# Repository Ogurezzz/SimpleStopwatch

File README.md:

# SimpleStopwatch

This is very simple stopwatch. I needed something that will count time when switch is On and reset when switch is off.
I found several solutions, but most of them are hardware worktime/switchOn counter. And you need to do some workaround to reset counter.

This SimpleStopwatch will solve my problem. It can count up to 99 hours. Uses up to 6 7-segment digits.

ToDo: 
1) (DONE) Make PCB with Atmega328, quartz, ULN2003 and indicators. With remote button/switch connection.
2) (DONE)Make 3D printed and CNC milled case for this Stopwatch. It should give me option for mounting to the panel of any device.

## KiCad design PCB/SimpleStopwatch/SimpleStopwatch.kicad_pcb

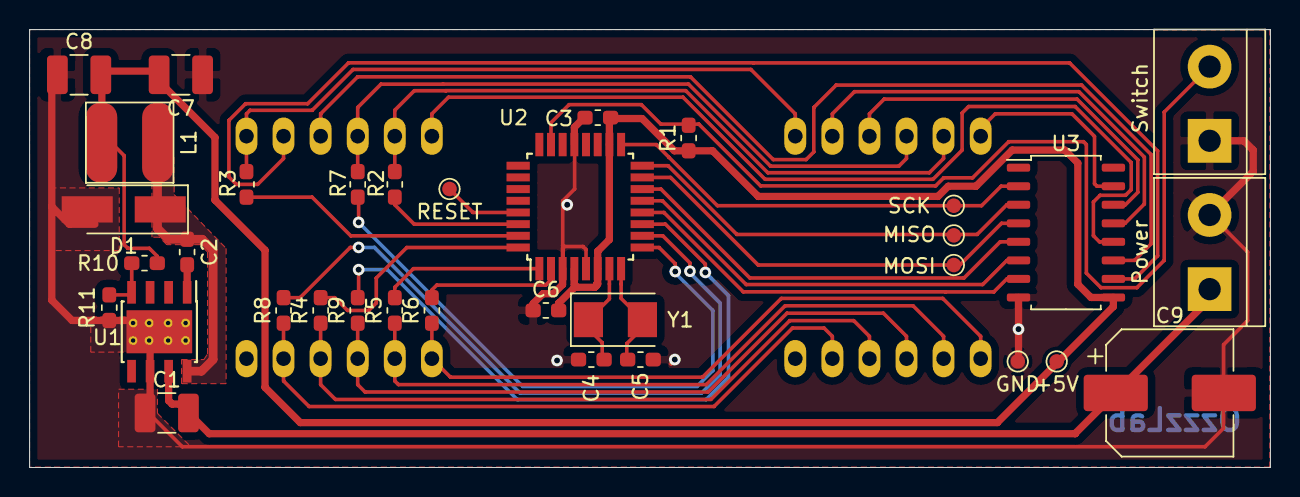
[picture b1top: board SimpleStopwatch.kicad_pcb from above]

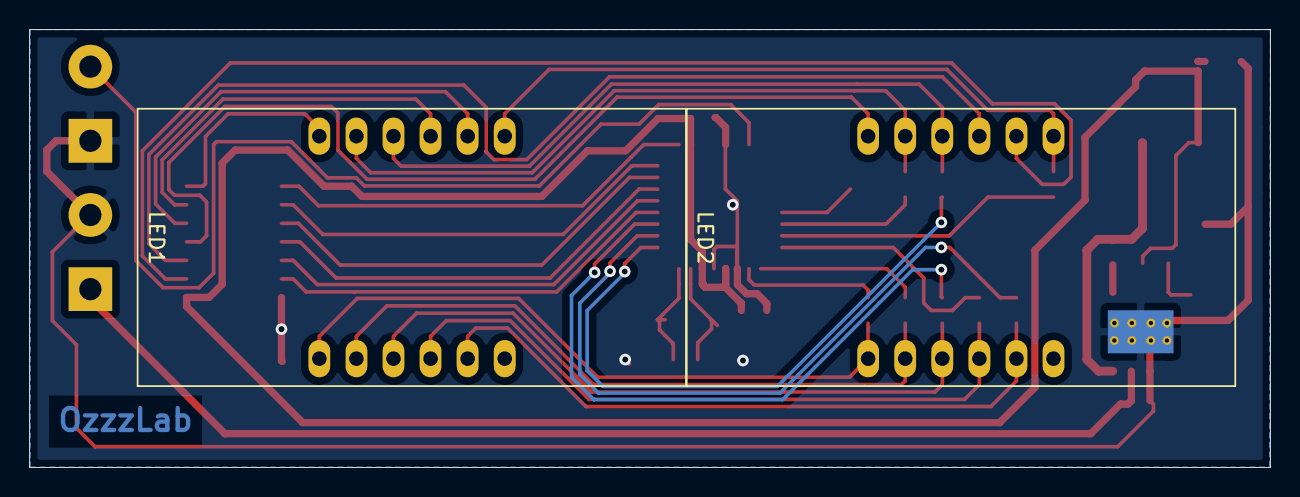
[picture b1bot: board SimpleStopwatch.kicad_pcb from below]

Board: 2 copper layers, 85.0 x 30.0 mm, 36 parts (2 on the bottom side), 38 nets.

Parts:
C1, C7, C8: 22u; C_1210_3225Metric_Pad1.42x2.65mm_HandSolder
C2, C3, C6: 0.1u; C_0603_1608Metric_Pad1.05x0.95mm_HandSolder
C4, C5: 22p; C_0603_1608Metric_Pad1.05x0.95mm_HandSolder
C9: 100uF; CP_Elec_8x10.5
D1: B120-E3; D_SMA_Handsoldering
H1: RESET; TestPoint_Pad_D1.0mm
H2: MOSI; TestPoint_Pad_D1.0mm
H3: MISO; TestPoint_Pad_D1.0mm
H4: SCK; TestPoint_Pad_D1.0mm
H5: +5V; TestPoint_Pad_D1.0mm
H6: GND; TestPoint_Pad_D1.0mm
J1: Switch; TerminalBlock_bornier-2_P5.08mm
J2: Power; TerminalBlock_bornier-2_P5.08mm
L1: L_Small; Inductor_CD54_Sumida
LED1, LED2: 7SEG_3DIG_CC_v2; LED_7SEG_3DIG_CC_0.56
R1: R_Small; R_0603_1608Metric_Pad1.05x0.95mm_HandSolder
R2, R3, R4, R5, R6, R7, R8, R9: 1k; R_0603_1608Metric_Pad1.05x0.95mm_HandSolder
R10: 5.1k; R_0603_1608Metric_Pad1.05x0.95mm_HandSolder
R11: 1.8k; R_0603_1608Metric_Pad1.05x0.95mm_HandSolder
U1: TPS5430DDA; TI_SO-PowerPAD-8_ThermalVias
U2: ATmega328P-AU; TQFP-32_7x7mm_P0.8mm
U3: ULN2003; SOIC-16_4.55x10.3mm_P1.27mm
Y1: Crystal_Small; Crystal_SMD_5032-2Pin_5.0x3.2mm

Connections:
+5V: C3.1, C6.2, C7.2, C8.2, H5.1, L1.2, R1.1, R10.2, U2.4, U2.6, U2.18, U3.9
+24V: C1.2, C9.1, J2.1, U1.7
Dig1: U2.12, U3.7
Dig2: U2.13, U3.6
Dig3: U2.14, U3.5
Dig4: H2.1, U2.15, U3.4
Dig5: H3.1, U2.16, U3.3
Dig6: H4.1, U2.17, U3.2
GND: C1.1, C3.2, C4.1, C5.2, C6.1, C7.1, C8.1, C9.2, D1.2, H6.1, J1.1, J2.2, R11.1, U1.6, U1.9, U2.3, U2.5, U2.21, U3.8
unnamed: C2.1, D1.1, L1.1, U1.8
unnamed: C2.2, U1.1
unnamed: C4.2, U2.7, Y1.1
unnamed: C5.1, U2.8, Y1.2
unnamed: H1.1, U2.29
unnamed: LED1.DIG1, U3.15
unnamed: LED1.DIG2, U3.14
unnamed: LED1.DIG3, U3.13
unnamed: LED2.DIG1, U3.12
unnamed: LED2.DIG2, U3.11
unnamed: LED2.DIG3, U3.10
unnamed: R2.2, U2.30
unnamed: R3.2, U2.31
unnamed: R4.2, U2.32
unnamed: R5.2, U2.1
unnamed: R6.2, U2.2
unnamed: R7.2, U2.9
unnamed: R8.2, U2.10
unnamed: R9.2, U2.11
unnamed: R10.1, R11.2, U1.4
SW: J1.2, R1.2, U2.23
SegA: LED1.A, LED2.A, R2.1
SegB: LED1.B, LED2.B, R3.1
SegC: LED1.C, LED2.C, R4.1
SegD: LED1.D, LED2.D, R5.1
SegE: LED1.E, LED2.E, R6.1
SegF: LED1.F, LED2.F, R7.1
SegG: LED1.G, LED2.G, R8.1
SegP: LED1.DP, LED2.DP, R9.1

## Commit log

2021-05-18 Initial upload
2021-05-19 added signature.h
2021-06-10 Added KiCAD PCB
2021-06-10 Changed to correct 8MHz quartz
2021-06-10 Added support of Direct connection to shiftLED lib
2021-06-10 Direct connection support
2021-06-10 Changed configuration
2021-06-11 Removed ULN2003 Mistake
2021-06-11 Changed LDO to DCDC module board
2021-06-11 Mini360 little changes
2021-06-11 PCB Release v0.2
2021-06-11 Some PCB improvements
2021-06-11 release 1.0
2021-06-12 code cleanup
2021-06-15 PCB with Mini360 module
2021-06-15 PCB updates
2021-06-15 Some code clean
2021-06-15 Added TPS5430 DCDC. Yuri version
2021-06-15 PCB Pictures
2021-06-15 Added Images
2021-06-15 Changed 3D model for 7-seg indicator
2021-06-29 PCB Improvements. C0603 to C1210
2021-06-29 PCB Changes. Size of capacitors
2022-01-09 Synchronosation
2022-07-19 Update .gitignore, main.c, and 22 more files...
